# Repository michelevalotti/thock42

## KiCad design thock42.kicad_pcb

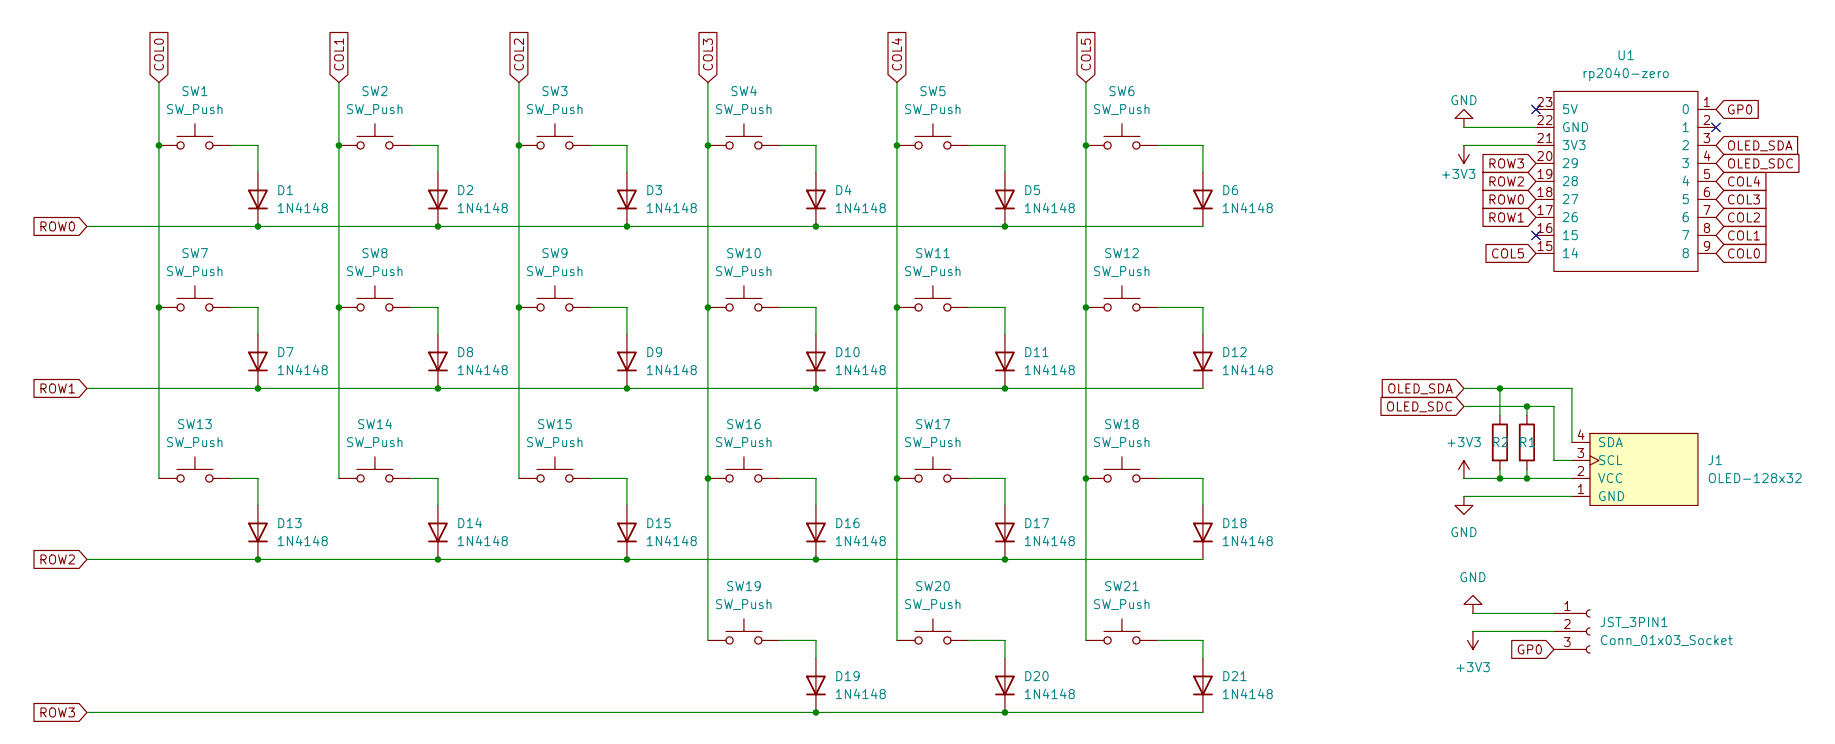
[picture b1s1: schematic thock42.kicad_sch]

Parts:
D1, D2, D3, D4, D5, D6, D7, D8, D9, D10, D11, D12, D13, D14, D15, D16, D17, D18, D19, D20, D21: 1N4148; D_DO-35_SOD27_P7.62mm_Horizontal
J1: OLED-128x32; OLED-128x32-double-sided
JST_3PIN1: Conn_01x03_Socket; JST_PH_S3B-PH-K_1x03_P2.00mm_Horizontal
R1, R2: R; R_Axial_DIN0207_L6.3mm_D2.5mm_P10.16mm_Horizontal
SW1, SW2, SW3, SW4, SW5, SW6, SW7, SW8, SW9, SW10, SW11, SW12, SW13, SW14, SW15, SW16, SW17, SW18, SW19, SW20, SW21: SW_Push; pg1350-RH_silkscreen
U1: rp2040-zero; rp2040-zero-tht_nobtm_reversible

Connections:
+3V3: J1.2 (VCC), JST_3PIN1.2, R1.2, R2.2, U1.21 (3V3); also elsewhere on the board
COL0: SW1.1, SW7.1, SW13.1, U1.9 (8)
COL1: SW2.1, SW8.1, SW14.1, U1.8 (7)
COL2: SW3.1, SW9.1, SW15.1, U1.7 (6)
COL3: SW4.1, SW10.1, SW16.1, SW19.1, U1.6 (5)
COL4: SW5.1, SW11.1, SW17.1, SW20.1, U1.5 (4)
COL5: SW6.1, SW12.1, SW18.1, SW21.1, U1.15 (14)
GND: J1.1 (GND), JST_3PIN1.1, U1.22 (GND); also elsewhere on the board
GP0: JST_3PIN1.3, U1.1 (0); also elsewhere on the board
unnamed: D1.2 (A), SW1.2
unnamed: D2.2 (A), SW2.2
unnamed: D3.2 (A), SW3.2
unnamed: D4.2 (A), SW4.2
unnamed: D5.2 (A), SW5.2
unnamed: D6.2 (A), SW6.2
unnamed: D7.2 (A), SW7.2
unnamed: D8.2 (A), SW8.2
unnamed: D9.2 (A), SW9.2
unnamed: D10.2 (A), SW10.2
unnamed: D11.2 (A), SW11.2
unnamed: D12.2 (A), SW12.2
unnamed: D13.2 (A), SW13.2
unnamed: D14.2 (A), SW14.2
unnamed: D15.2 (A), SW15.2
unnamed: D16.2 (A), SW16.2
unnamed: D17.2 (A), SW17.2
unnamed: D18.2 (A), SW18.2
unnamed: D19.2 (A), SW19.2
unnamed: D20.2 (A), SW20.2
unnamed: D21.2 (A), SW21.2
OLED_SDA: J1.4 (SDA), R2.1, U1.3 (2)
OLED_SDC: J1.3 (SCL), R1.1, U1.4 (3)
ROW0: D1.1 (K), D2.1 (K), D3.1 (K), D4.1 (K), D5.1 (K), D6.1 (K), U1.18 (27)
ROW1: D7.1 (K), D8.1 (K), D9.1 (K), D10.1 (K), D11.1 (K), D12.1 (K), U1.17 (26)
ROW2: D13.1 (K), D14.1 (K), D15.1 (K), D16.1 (K), D17.1 (K), D18.1 (K), U1.19 (28)
ROW3: D19.1 (K), D20.1 (K), D21.1 (K), U1.20 (29)

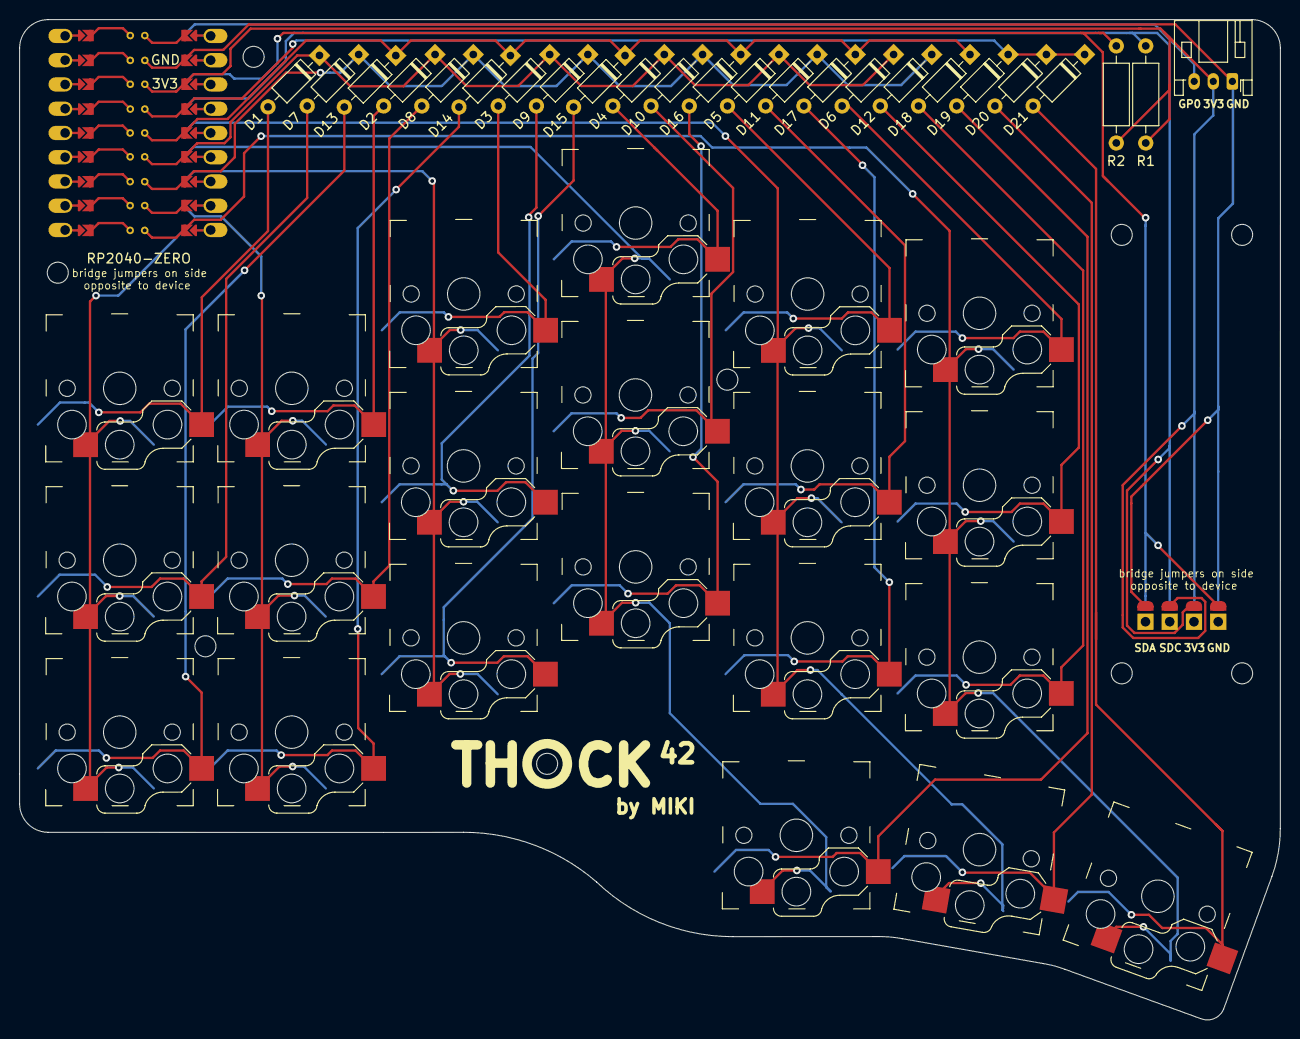
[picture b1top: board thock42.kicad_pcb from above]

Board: 2 copper layers, 132.0 x 104.7 mm, 47 parts (0 on the bottom side), 36 nets.

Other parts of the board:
JST_3PIN: Conn_01x03_Socket; JST_PH_S3B-PH-K_1x03_P2.00mm_Horizontal

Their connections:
+3V3: JST_3PIN.2; also elsewhere on the board
GND: JST_3PIN.1; also elsewhere on the board
GP0: JST_3PIN.3; also elsewhere on the board

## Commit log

2024-04-04 first commit: schematics and pcb
2024-04-05 fix: add ignore for .lck files
2024-04-05 4pin jst with i2c changed to 3pin jst with serial
2024-04-08 feat: add switch id silkscreen
2024-04-11 feat: add more mounting holes
2024-04-14 add symbols and footprints libraries
2024-04-14 add ignore for .bak files
2024-04-14 update links to libs, jst footprint, and add add mounting hole
2024-04-23 fix: add freecad files
2024-05-23 feat: add simple keycap 3d model
2024-05-23 add i2c pullups and redesign thumb cluster
2024-05-23 add space between resistors and change some silkscreen labels
2024-05-26 moev thumb cluster down by .2mm
2024-05-26 18x18mm keycap
2024-05-26 adapt to symmetric keycap spacing
2024-05-26 fix clearance errors
2024-05-26 move mounting point
2024-05-30 add silkscreen for resistors on backside
2024-06-02 remove/ignore prl files
2024-06-02 remove/ignore prl file
2024-06-02 add resistor silkscreen on back layer
2024-06-29 move index col down to align with ring col
2024-06-29 move index col down to match ring col and fix tolerance error
